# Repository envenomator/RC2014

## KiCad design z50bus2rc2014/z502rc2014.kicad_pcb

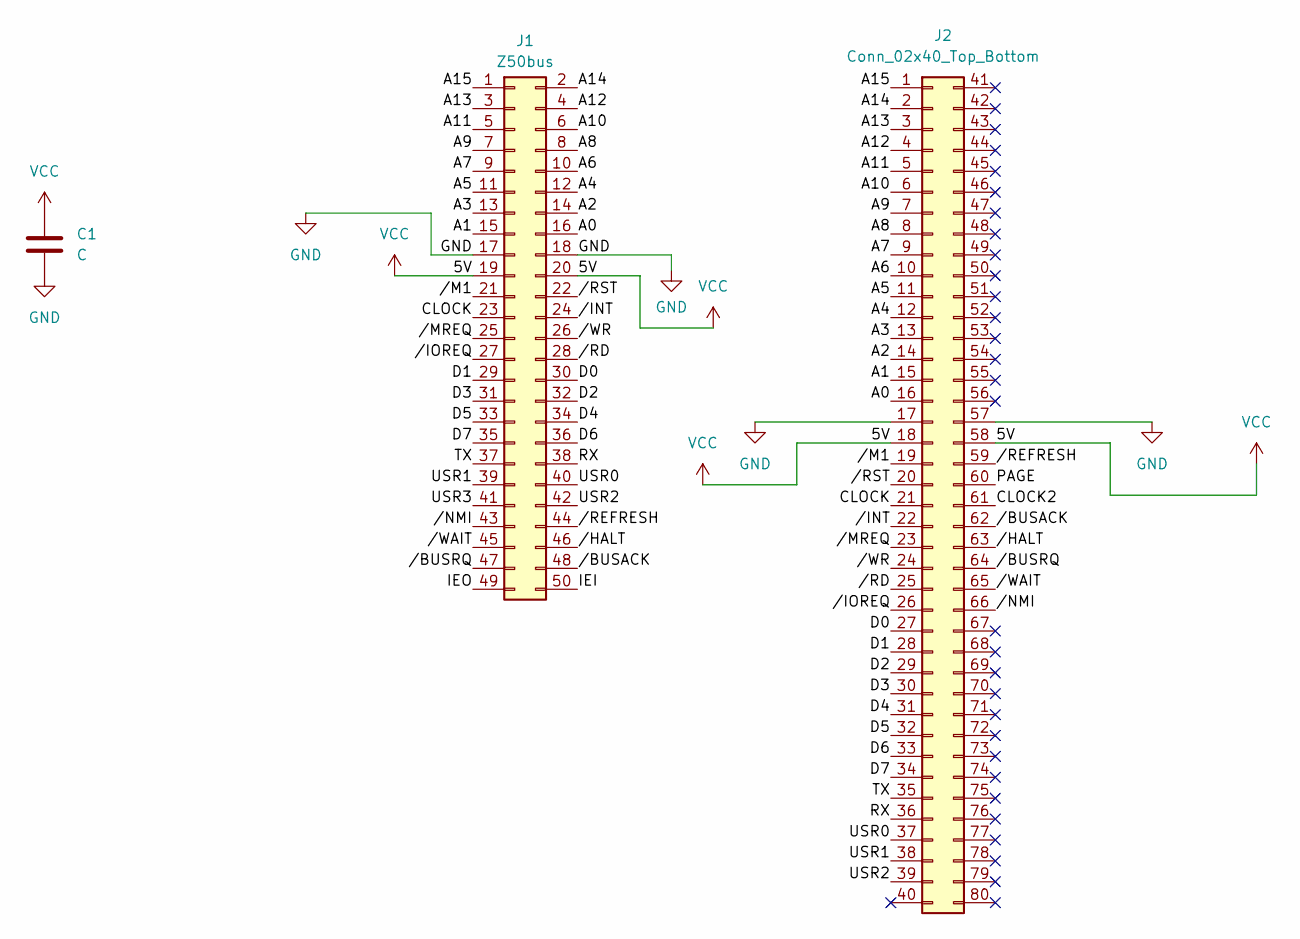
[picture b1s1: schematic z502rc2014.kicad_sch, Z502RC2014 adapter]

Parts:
C1: C; C_Disc_D3.0mm_W1.6mm_P2.50mm
J1: Z50bus; z50bus_edge
J2: Conn_02x40_Top_Bottom; rc2014_edge

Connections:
/A0: J1.16, J2.16
/A1: J1.15, J2.15
/A2: J1.14, J2.14
/A3: J1.13, J2.13
/A4: J1.12, J2.12
/A5: J1.11, J2.11
/A6: J1.10, J2.10
/A7: J1.9, J2.9
/A8: J1.8, J2.8
/A9: J1.7, J2.7
/A10: J1.6, J2.6
/A11: J1.5, J2.5
/A12: J1.4, J2.4
/A13: J1.3, J2.3
/A14: J1.2, J2.2
/A15: J1.1, J2.1
/CLOCK: J1.23, J2.21
/CLOCK2: J2.61
/D0: J1.30, J2.27
/D1: J1.29, J2.28
/D2: J1.32, J2.29
/D3: J1.31, J2.30
/D4: J1.34, J2.31
/D5: J1.33, J2.32
/D6: J1.36, J2.33
/D7: J1.35, J2.34
/IEI: J1.50
/IEO: J1.49
/PAGE: J2.60
/RX: J1.38, J2.36
/TX: J1.37, J2.35
/USR0: J1.40, J2.37
/USR1: J1.39, J2.38
/USR2: J1.42, J2.39
/USR3: J1.41
//BUSACK: J1.48, J2.62
//BUSRQ: J1.47, J2.64
//HALT: J1.46, J2.63
//INT: J1.24, J2.22
//IOREQ: J1.27, J2.26
//M1: J1.21, J2.19
//MREQ: J1.25, J2.23
//NMI: J1.43, J2.66
//RD: J1.28, J2.25
//REFRESH: J1.44, J2.59
//RST: J1.22, J2.20
//WAIT: J1.45, J2.65
//WR: J1.26, J2.24
GND: C1.2, J1.17, J1.18, J2.17, J2.57
VCC: C1.1, J1.19, J1.20, J2.18, J2.58

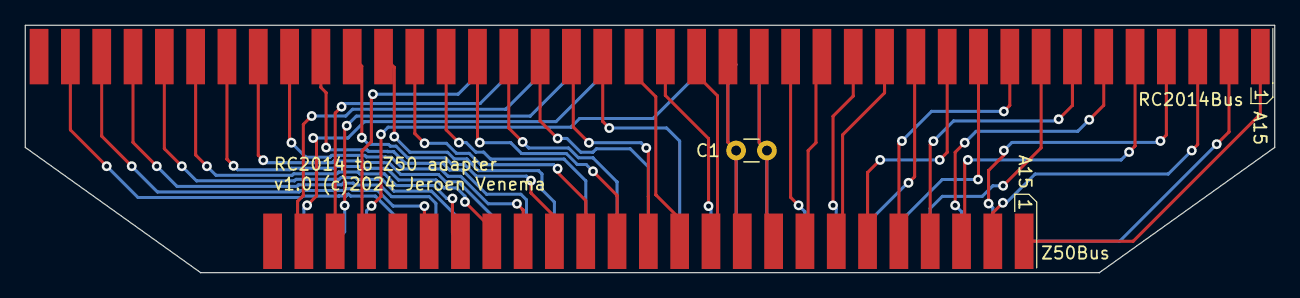
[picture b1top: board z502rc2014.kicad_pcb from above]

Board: 2 copper layers, 101.3 x 20.1 mm, 3 parts (0 on the bottom side), 45 nets.

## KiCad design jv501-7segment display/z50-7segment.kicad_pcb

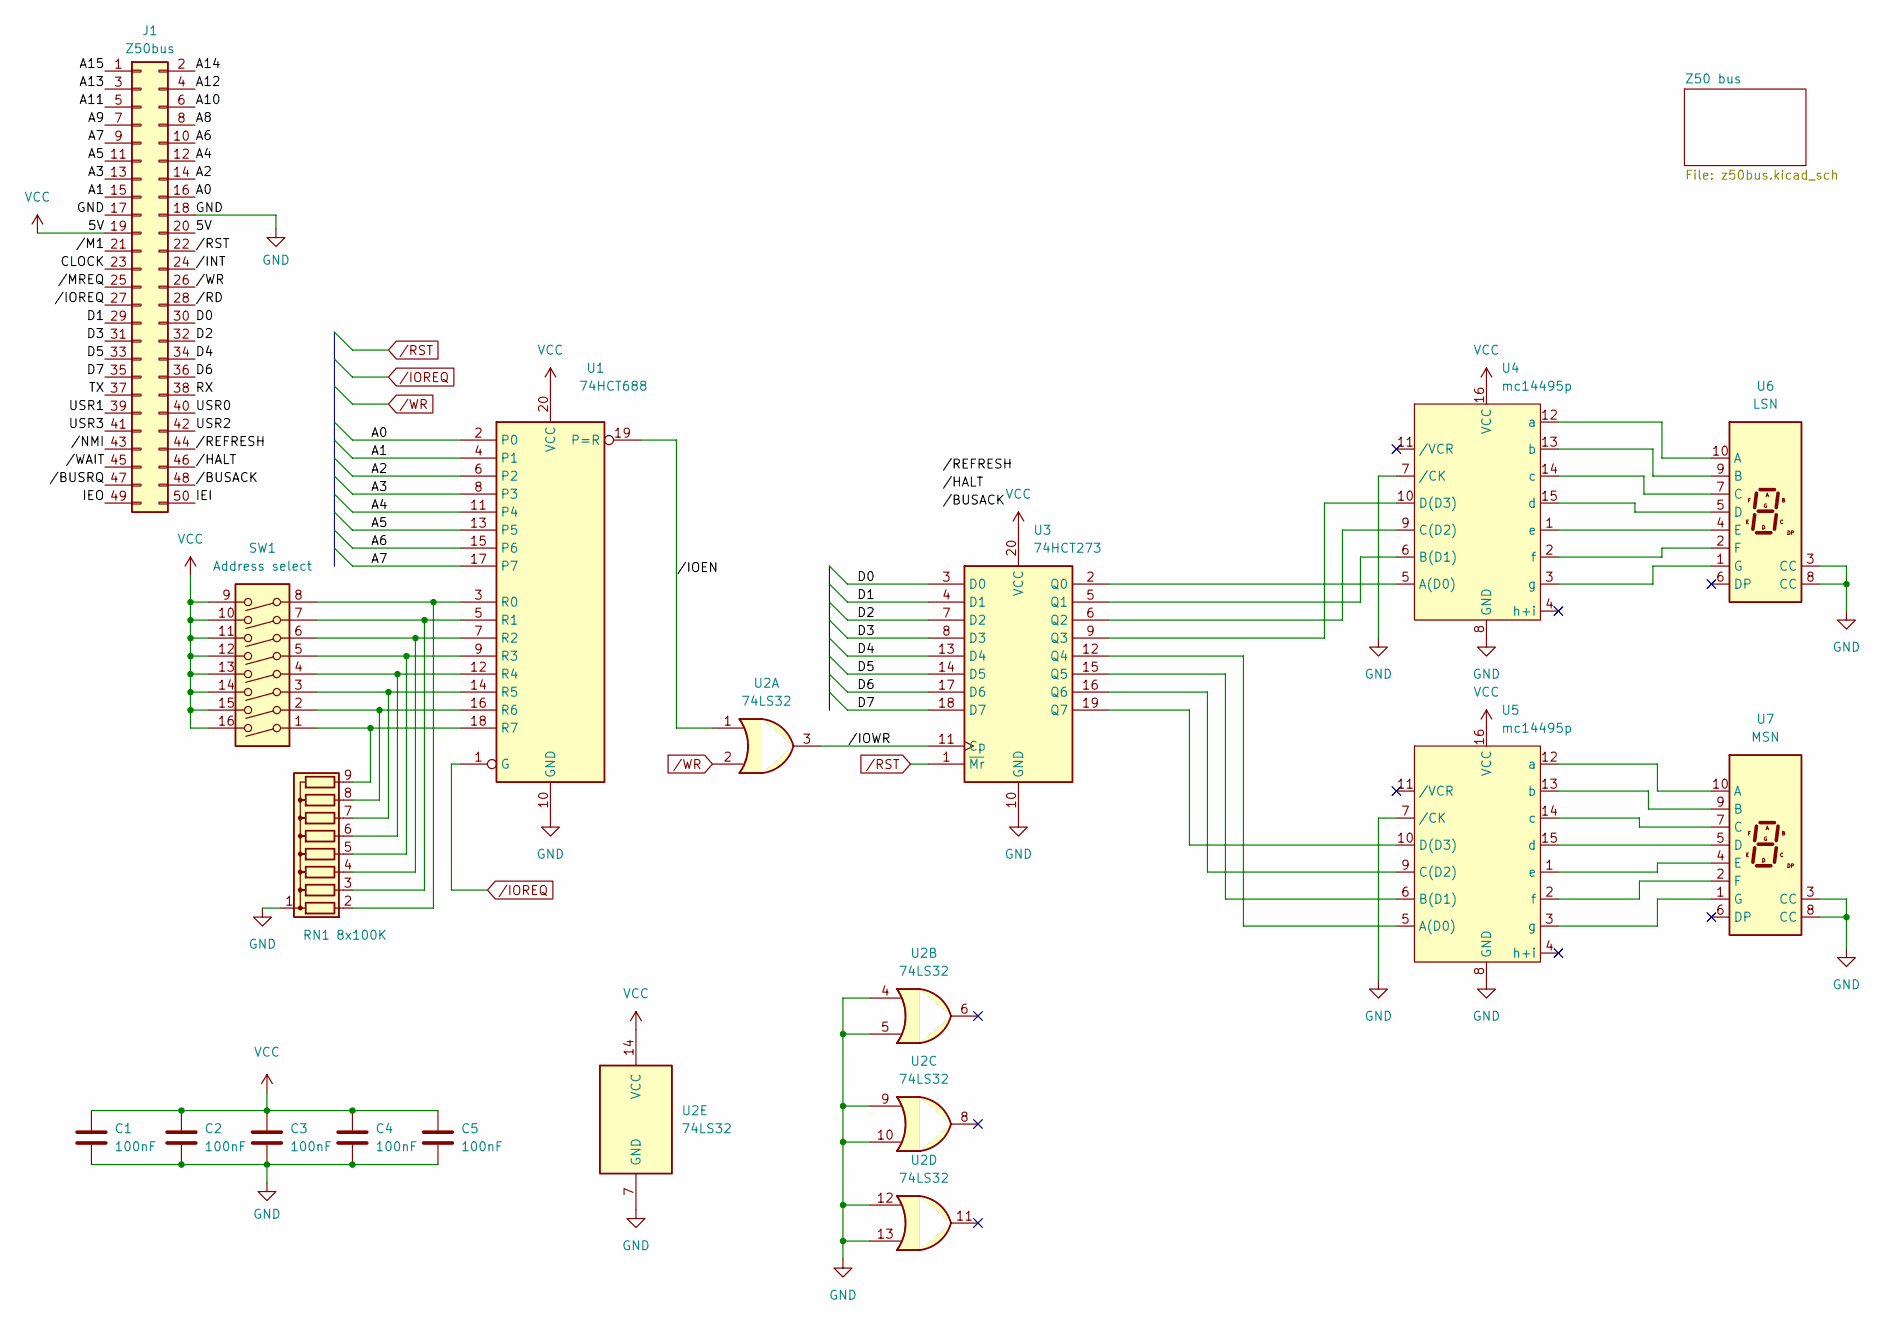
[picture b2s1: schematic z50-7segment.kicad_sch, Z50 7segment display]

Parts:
C1, C2, C3, C4, C5: 100nF; C_Disc_D3.8mm_W2.6mm_P2.50mm
J1: Z50bus; PinHeader_2x25_P2.54mm_Horizontal
RN1: 8x100K; R_Array_SIP9
SW1: Address select; DIP-16_W7.62mm
U1: 74HCT688; DIP-20_W7.62mm_Socket_LongPads
U2: 74LS32; DIP-14_W7.62mm_Socket_LongPads
U3: 74HCT273; DIP-20_W7.62mm_Socket_LongPads
U4, U5: mc14495p; DIP-16_W7.62mm_Socket_LongPads
U6: LSN; Sx39-1xxxxx
U7: MSN; Sx39-1xxxxx

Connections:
/A0: J1.16, U1.2 (P0)
/A1: J1.15, U1.4 (P1)
/A2: J1.14, U1.6 (P2)
/A3: J1.13, U1.8 (P3)
/A4: J1.12, U1.11 (P4)
/A5: J1.11, U1.13 (P5)
/A6: J1.10, U1.15 (P6)
/A7: J1.9, U1.17 (P7)
/A8: J1.8
/A9: J1.7
/A10: J1.6
/A11: J1.5
/A12: J1.4
/A13: J1.3
/A14: J1.2
/A15: J1.1
/CLOCK: J1.23
/D0: J1.30, U3.3 (D0)
/D1: J1.29, U3.4 (D1)
/D2: J1.32, U3.7 (D2)
/D3: J1.31, U3.8 (D3)
/D4: J1.34, U3.13 (D4)
/D5: J1.33, U3.14 (D5)
/D6: J1.36, U3.17 (D6)
/D7: J1.35, U3.18 (D7)
/IEI: J1.50
/IEO: J1.49
/RX: J1.38
/TX: J1.37
/USR0: J1.40
/USR1: J1.39
/USR2: J1.42
/USR3: J1.41
//BUSACK: J1.48
//BUSRQ: J1.47
//HALT: J1.46
//INT: J1.24
//IOEN: U1.19 (P=R), U2.1
//IOWR: U2.3, U3.11 (Cp)
//M1: J1.21
//MREQ: J1.25
//NMI: J1.43
//RD: J1.28
//REFRESH: J1.44
//WAIT: J1.45
GND: C1.2, C2.2, C3.2, C4.2, C5.2, J1.17, J1.18, RN1.1 (common), U1.10 (GND), U2.4, U2.5, U2.7 (GND), U2.9, U2.10, U2.12, U2.13, U3.10 (GND), U4.7 (/CK), U4.8 (GND), U5.7 (/CK), U5.8 (GND), U6.3 (CC), U6.8 (CC), U7.3 (CC), U7.8 (CC)
unnamed: RN1.2 (R1), SW1.8, U1.3 (R0)
unnamed: RN1.3 (R2), SW1.7, U1.5 (R1)
unnamed: RN1.4 (R3), SW1.6, U1.7 (R2)
unnamed: RN1.5 (R4), SW1.5, U1.9 (R3)
unnamed: RN1.6 (R5), SW1.4, U1.12 (R4)
unnamed: RN1.7 (R6), SW1.3, U1.14 (R5)
unnamed: RN1.8 (R7), SW1.2, U1.16 (R6)
unnamed: RN1.9 (R8), SW1.1, U1.18 (R7)
unnamed: U3.2 (Q0), U4.5 (A(D0))
unnamed: U3.5 (Q1), U4.6 (B(D1))
unnamed: U3.6 (Q2), U4.9 (C(D2))
unnamed: U3.9 (Q3), U4.10 (D(D3))
unnamed: U3.12 (Q4), U5.5 (A(D0))
unnamed: U3.15 (Q5), U5.6 (B(D1))
unnamed: U3.16 (Q6), U5.9 (C(D2))
unnamed: U3.19 (Q7), U5.10 (D(D3))
unnamed: U4.1 (e), U6.4 (E)
unnamed: U4.2 (f), U6.2 (F)
unnamed: U4.3 (g), U6.1 (G)
unnamed: U4.12 (a), U6.10 (A)
unnamed: U4.13 (b), U6.9 (B)
unnamed: U4.14 (c), U6.7 (C)
unnamed: U4.15 (d), U6.5 (D)
unnamed: U5.1 (e), U7.4 (E)
unnamed: U5.2 (f), U7.2 (F)
unnamed: U5.3 (g), U7.1 (G)
unnamed: U5.12 (a), U7.10 (A)
unnamed: U5.13 (b), U7.9 (B)
unnamed: U5.14 (c), U7.7 (C)
unnamed: U5.15 (d), U7.5 (D)
VCC: C1.1, C2.1, C3.1, C4.1, C5.1, J1.19, J1.20, SW1.9, SW1.10, SW1.11, SW1.12, SW1.13, SW1.14, SW1.15, SW1.16, U1.20 (VCC), U2.14 (VCC), U3.20 (VCC), U4.16 (VCC), U5.16 (VCC)
/IOREQ: J1.27, U1.1 (G)
/RST: J1.22, U3.1 (~Mr)
/WR: J1.26, U2.2

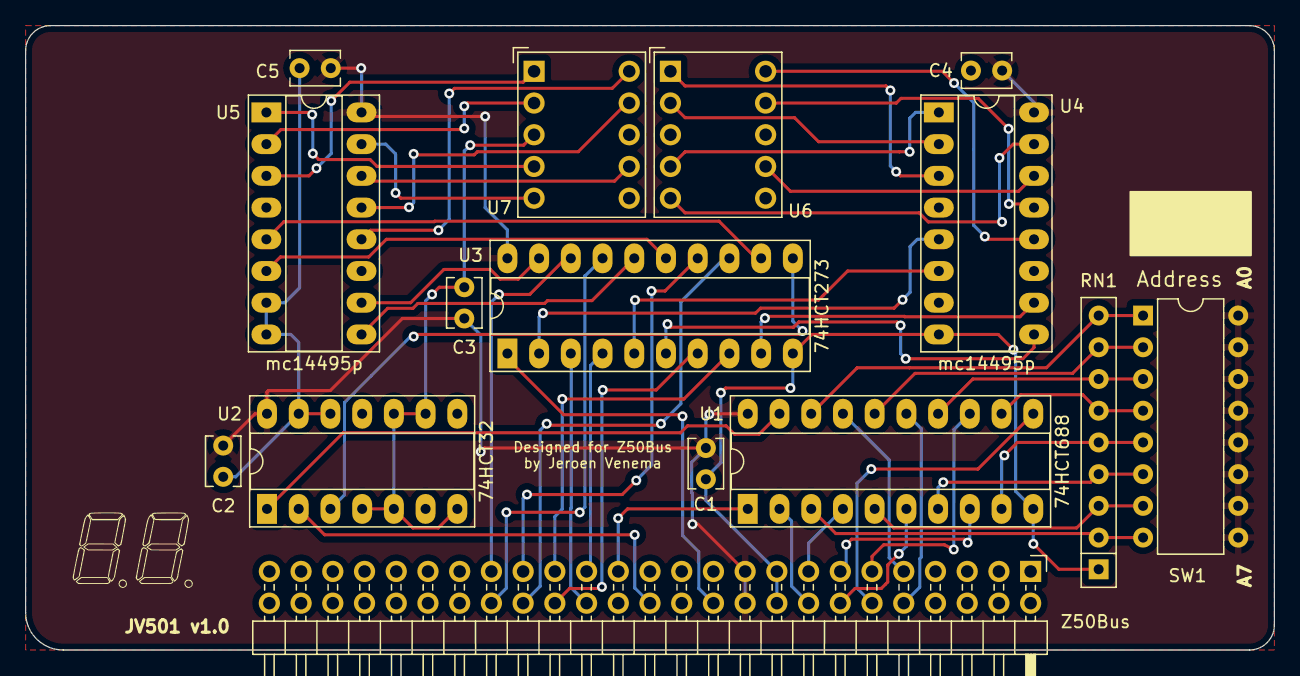
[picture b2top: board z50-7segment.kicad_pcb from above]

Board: 2 copper layers, 100.0 x 50.0 mm, 15 parts (0 on the bottom side), 53 nets.

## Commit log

2022-12-03 Project jv501 added
2022-12-03 Added 7segment step files for display
2024-06-22 Added rc2014 adapter, as ordered

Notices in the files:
z50bus2rc2014/z502rc2014.kicad_pcb:
v1.0 (c)2024 Jeroen Venema
